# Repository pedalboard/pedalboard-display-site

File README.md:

# pedalboard-display-site

Source code for github pages avalilable from https://pedalboard.github.io/pedalboard-display-site

This is mostly generated. Do not edit directly!

* latest is generated from main
* latest-x is generated from branch x
* vX.Y.Z are the released versions
* stable points to the current stable release

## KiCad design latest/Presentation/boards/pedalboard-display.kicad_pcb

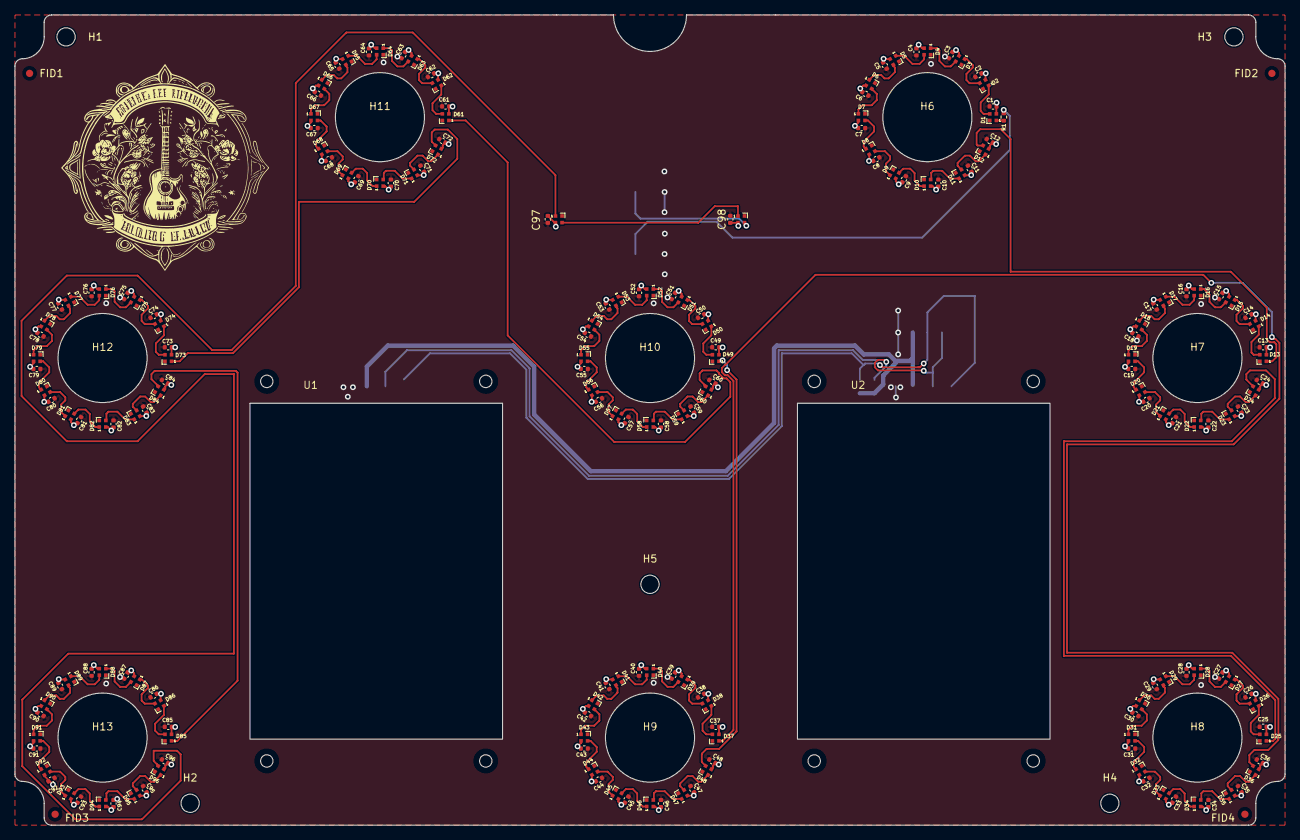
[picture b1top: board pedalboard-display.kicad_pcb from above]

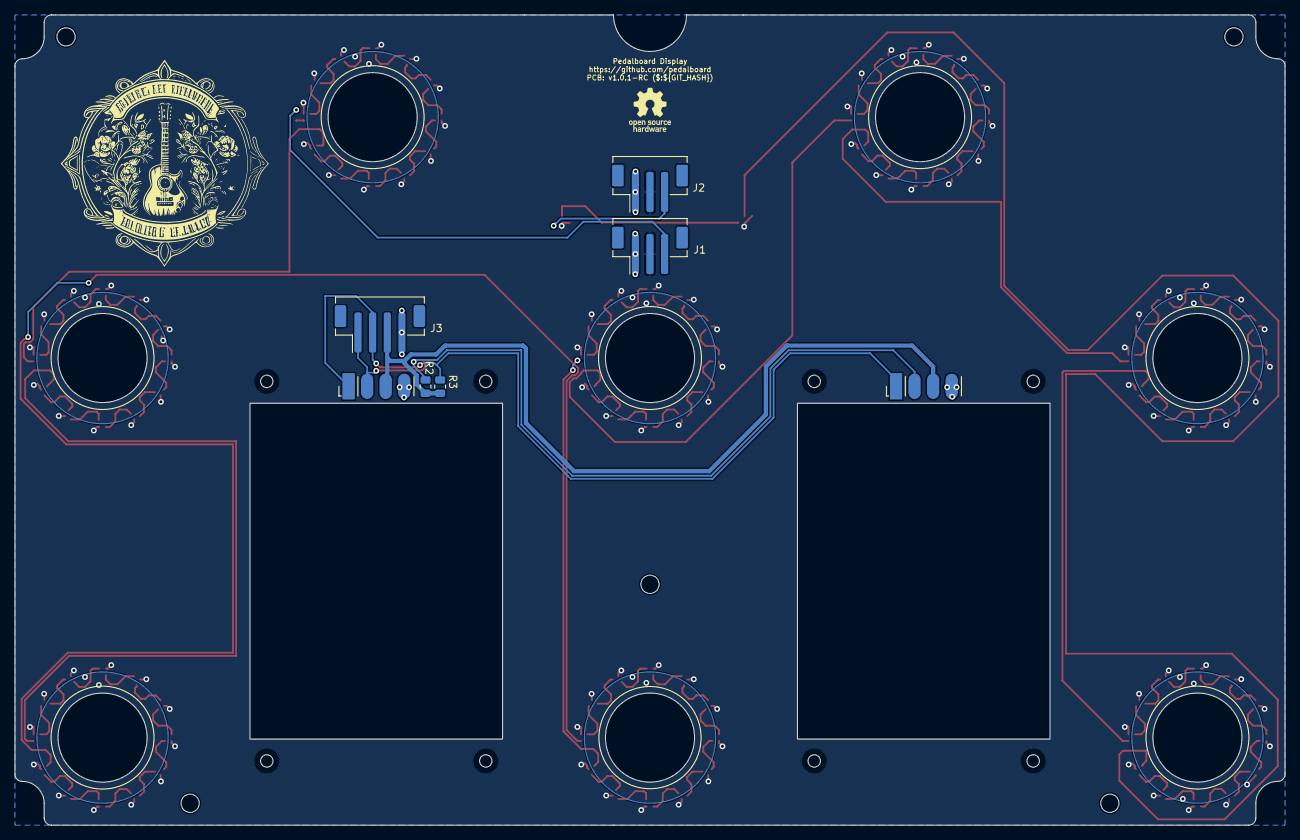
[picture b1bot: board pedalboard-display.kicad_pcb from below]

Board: 2 copper layers, 174.0 x 111.0 mm, 222 parts (6 on the bottom side), 105 nets.

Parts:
C1, C2, C3, C4, C5, C6, C7, C8, C9, C10, C11, C12, C13, C14, C15, C16, C17, C18, C19, C20, C21, C22, C23, C24, C25, C26, C27, C28, C29, C30, C31, C32, C33, C34, C35, C36, C37, C38, C39, C40, C41, C42, C43, C44, C45, C46, C47, C48, C49, C50, C51, C52, C53, C54, C55, C56, C57, C58, C59, C60, C61, C62, C63, C64, C65, C66, C67, C68, C69, C70, C71, C72, C73, C74, C75, C76, C77, C78, C79, C80, C81, C82, C83, C84, C85, C86, C87, C88, C89, C90, C91, C92, C93, C94, C95, C96, C97, C98: 1uF; C_0402_1005Metric
D1, D2, D3, D4, D5, D6, D7, D8, D9, D10, D11, D12, D13, D14, D15, D16, D17, D18, D19, D20, D21, D22, D23, D24, D25, D26, D27, D28, D29, D30, D31, D32, D33, D34, D35, D36, D37, D38, D39, D40, D41, D42, D43, D44, D45, D46, D47, D48, D49, D50, D51, D52, D53, D54, D55, D56, D57, D58, D59, D60, D61, D62, D63, D64, D65, D66, D67, D68, D69, D70, D71, D72, D73, D74, D75, D76, D77, D78, D79, D80, D81, D82, D83, D84, D85, D86, D87, D88, D89, D90, D91, D92, D93, D94, D95, D96, D97, D98: SK6812_EC15; LED_SK6812_EC15_1.5x1.5mm
FID1, FID2, FID3, FID4: Fiducial; Fiducial_1mm_Mask2mm
H1, H2, H3, H4, H5: MountingHole; MountingHole_2.5mm
H6, H11: Actuator; ActuatorRotary
H7, H8, H9, H10, H12, H13: Actuator
J1, J2: JST PH 3; JST_PH_B3B-PH-SM4-TB_1x03-1MP_P2.00mm_Vertical
J3: JST PH 4; JST_PH_B4B-PH-SM4-TB_1x04-1MP_P2.00mm_Vertical
R1: 330; R_0402_1005Metric
R2, R3: 3K3; R_0805_2012Metric
SYM1: Logo_Open_Hardware_Small; OSHW-Logo_5.7x6mm_SilkScreen
U1, U2: OLED I2C; OLED_128x128

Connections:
+3.3V: J3.3, R2.1, R3.1, U1.3 (VDD), U2.3 (VDD)
/I2C_SCL: J3.1, R2.2, U1.2 (SCL), U2.2 (SCL)
/I2C_SDA: J3.2, R3.2, U1.1 (SDA), U2.1 (SDA)
/Led Ring A/D_IN: D84.3 (DOUT), D85.1 (DIN)
/Led Ring A/D_OUT: D96.3 (DOUT), D97.1 (DIN)
/Led Ring B/D_IN: D36.3 (DOUT), D37.1 (DIN)
/Led Ring B/D_OUT: D48.3 (DOUT), D49.1 (DIN)
/Led Ring C/D_IN: D24.3 (DOUT), D25.1 (DIN)
/Led Ring D/D_IN: D72.3 (DOUT), D73.1 (DIN)
/Led Ring E/D_OUT: D60.3 (DOUT), D61.1 (DIN)
/Led Ring F/D_IN: D12.3 (DOUT), D13.1 (DIN)
/Led Ring GAIN/D_IN: D1.1 (DIN), R1.2
GND: C1.2, C2.2, C3.2, C4.2, C5.2, C6.2, C7.2, C8.2, C9.2, C10.2, C11.2, C12.2, C13.2, C14.2, C15.2, C16.2, C17.2, C18.2, C19.2, C20.2, C21.2, C22.2, C23.2, C24.2, C25.2, C26.2, C27.2, C28.2, C29.2, C30.2, C31.2, C32.2, C33.2, C34.2, C35.2, C36.2, C37.2, C38.2, C39.2, C40.2, C41.2, C42.2, C43.2, C44.2, C45.2, C46.2, C47.2, C48.2, C49.2, C50.2, C51.2, C52.2, C53.2, C54.2, C55.2, C56.2, C57.2, C58.2, C59.2, C60.2, C61.2, C62.2, C63.2, C64.2, C65.2, C66.2, C67.2, C68.2, C69.2, C70.2, C71.2, C72.2, C73.2, C74.2, C75.2, C76.2, C77.2, C78.2, C79.2, C80.2, C81.2, C82.2, C83.2, C84.2, C85.2, C86.2, C87.2, C88.2, C89.2, C90.2, C91.2, C92.2, C93.2, C94.2, C95.2, C96.2, C97.2, C98.2, D1.4 (VSS), D2.4 (VSS), D3.4 (VSS), D4.4 (VSS), D5.4 (VSS), D6.4 (VSS), D7.4 (VSS), D8.4 (VSS), D9.4 (VSS), D10.4 (VSS), D11.4 (VSS), D12.4 (VSS), D13.4 (VSS), D14.4 (VSS), D15.4 (VSS), D16.4 (VSS), D17.4 (VSS), D18.4 (VSS), D19.4 (VSS), D20.4 (VSS), D21.4 (VSS), D22.4 (VSS), D23.4 (VSS), D24.4 (VSS), D25.4 (VSS), D26.4 (VSS), D27.4 (VSS), D28.4 (VSS), D29.4 (VSS), D30.4 (VSS), D31.4 (VSS), D32.4 (VSS), D33.4 (VSS), D34.4 (VSS), D35.4 (VSS), D36.4 (VSS), D37.4 (VSS), D38.4 (VSS), D39.4 (VSS), D40.4 (VSS), D41.4 (VSS), D42.4 (VSS), D43.4 (VSS), D44.4 (VSS), D45.4 (VSS), D46.4 (VSS), D47.4 (VSS), D48.4 (VSS), D49.4 (VSS), D50.4 (VSS), D51.4 (VSS), D52.4 (VSS), D53.4 (VSS), D54.4 (VSS), D55.4 (VSS), D56.4 (VSS), D57.4 (VSS), D58.4 (VSS), D59.4 (VSS), D60.4 (VSS), D61.4 (VSS), D62.4 (VSS), D63.4 (VSS), D64.4 (VSS), D65.4 (VSS), D66.4 (VSS), D67.4 (VSS), D68.4 (VSS), D69.4 (VSS), D70.4 (VSS), D71.4 (VSS), D72.4 (VSS), D73.4 (VSS), D74.4 (VSS), D75.4 (VSS), D76.4 (VSS), D77.4 (VSS), D78.4 (VSS), D79.4 (VSS), D80.4 (VSS), D81.4 (VSS), D82.4 (VSS), D83.4 (VSS), D84.4 (VSS), D85.4 (VSS), D86.4 (VSS), D87.4 (VSS), D88.4 (VSS), D89.4 (VSS), D90.4 (VSS), D91.4 (VSS), D92.4 (VSS), D93.4 (VSS), D94.4 (VSS), D95.4 (VSS), D96.4 (VSS), D97.4 (VSS), D98.4 (VSS), J1.1, J2.1, J3.4, U1.4 (VSS), U2.4 (VSS)
unnamed: D1.3 (DOUT), D2.1 (DIN)
unnamed: D2.3 (DOUT), D3.1 (DIN)
unnamed: D3.3 (DOUT), D4.1 (DIN)
unnamed: D4.3 (DOUT), D5.1 (DIN)
unnamed: D5.3 (DOUT), D6.1 (DIN)
unnamed: D6.3 (DOUT), D7.1 (DIN)
unnamed: D7.3 (DOUT), D8.1 (DIN)
unnamed: D8.3 (DOUT), D9.1 (DIN)
unnamed: D9.3 (DOUT), D10.1 (DIN)
unnamed: D10.3 (DOUT), D11.1 (DIN)
unnamed: D11.3 (DOUT), D12.1 (DIN)
unnamed: D13.3 (DOUT), D14.1 (DIN)
unnamed: D14.3 (DOUT), D15.1 (DIN)
unnamed: D15.3 (DOUT), D16.1 (DIN)
unnamed: D16.3 (DOUT), D17.1 (DIN)
unnamed: D17.3 (DOUT), D18.1 (DIN)
unnamed: D18.3 (DOUT), D19.1 (DIN)
unnamed: D19.3 (DOUT), D20.1 (DIN)
unnamed: D20.3 (DOUT), D21.1 (DIN)
unnamed: D21.3 (DOUT), D22.1 (DIN)
unnamed: D22.3 (DOUT), D23.1 (DIN)
unnamed: D23.3 (DOUT), D24.1 (DIN)
unnamed: D25.3 (DOUT), D26.1 (DIN)
unnamed: D26.3 (DOUT), D27.1 (DIN)
unnamed: D27.3 (DOUT), D28.1 (DIN)
unnamed: D28.3 (DOUT), D29.1 (DIN)
unnamed: D29.3 (DOUT), D30.1 (DIN)
unnamed: D30.3 (DOUT), D31.1 (DIN)
unnamed: D31.3 (DOUT), D32.1 (DIN)
unnamed: D32.3 (DOUT), D33.1 (DIN)
unnamed: D33.3 (DOUT), D34.1 (DIN)
unnamed: D34.3 (DOUT), D35.1 (DIN)
unnamed: D35.3 (DOUT), D36.1 (DIN)
unnamed: D37.3 (DOUT), D38.1 (DIN)
unnamed: D38.3 (DOUT), D39.1 (DIN)
unnamed: D39.3 (DOUT), D40.1 (DIN)
unnamed: D40.3 (DOUT), D41.1 (DIN)
unnamed: D41.3 (DOUT), D42.1 (DIN)
unnamed: D42.3 (DOUT), D43.1 (DIN)
unnamed: D43.3 (DOUT), D44.1 (DIN)
unnamed: D44.3 (DOUT), D45.1 (DIN)
unnamed: D45.3 (DOUT), D46.1 (DIN)
unnamed: D46.3 (DOUT), D47.1 (DIN)
unnamed: D47.3 (DOUT), D48.1 (DIN)
unnamed: D49.3 (DOUT), D50.1 (DIN)
unnamed: D50.3 (DOUT), D51.1 (DIN)
unnamed: D51.3 (DOUT), D52.1 (DIN)
unnamed: D52.3 (DOUT), D53.1 (DIN)
unnamed: D53.3 (DOUT), D54.1 (DIN)
unnamed: D54.3 (DOUT), D55.1 (DIN)
unnamed: D55.3 (DOUT), D56.1 (DIN)
unnamed: D56.3 (DOUT), D57.1 (DIN)
unnamed: D57.3 (DOUT), D58.1 (DIN)
unnamed: D58.3 (DOUT), D59.1 (DIN)
unnamed: D59.3 (DOUT), D60.1 (DIN)
unnamed: D61.3 (DOUT), D62.1 (DIN)
unnamed: D62.3 (DOUT), D63.1 (DIN)
unnamed: D63.3 (DOUT), D64.1 (DIN)
unnamed: D64.3 (DOUT), D65.1 (DIN)
unnamed: D65.3 (DOUT), D66.1 (DIN)
unnamed: D66.3 (DOUT), D67.1 (DIN)
unnamed: D67.3 (DOUT), D68.1 (DIN)
unnamed: D68.3 (DOUT), D69.1 (DIN)
unnamed: D69.3 (DOUT), D70.1 (DIN)
unnamed: D70.3 (DOUT), D71.1 (DIN)
unnamed: D71.3 (DOUT), D72.1 (DIN)
unnamed: D73.3 (DOUT), D74.1 (DIN)
unnamed: D74.3 (DOUT), D75.1 (DIN)
unnamed: D75.3 (DOUT), D76.1 (DIN)
unnamed: D76.3 (DOUT), D77.1 (DIN)
unnamed: D77.3 (DOUT), D78.1 (DIN)
unnamed: D78.3 (DOUT), D79.1 (DIN)
unnamed: D79.3 (DOUT), D80.1 (DIN)
unnamed: D80.3 (DOUT), D81.1 (DIN)
unnamed: D81.3 (DOUT), D82.1 (DIN)
unnamed: D82.3 (DOUT), D83.1 (DIN)
unnamed: D83.3 (DOUT), D84.1 (DIN)
unnamed: D85.3 (DOUT), D86.1 (DIN)
unnamed: D86.3 (DOUT), D87.1 (DIN)
unnamed: D87.3 (DOUT), D88.1 (DIN)
unnamed: D88.3 (DOUT), D89.1 (DIN)
unnamed: D89.3 (DOUT), D90.1 (DIN)
unnamed: D90.3 (DOUT), D91.1 (DIN)
unnamed: D91.3 (DOUT), D92.1 (DIN)
unnamed: D92.3 (DOUT), D93.1 (DIN)
unnamed: D93.3 (DOUT), D94.1 (DIN)
unnamed: D94.3 (DOUT), D95.1 (DIN)
unnamed: D95.3 (DOUT), D96.1 (DIN)
unnamed: D97.3 (DOUT), D98.1 (DIN)
unnamed: D98.3 (DOUT), J2.3
unnamed: J1.3, R1.1
VCC: C1.1, C2.1, C3.1, C4.1, C5.1, C6.1, C7.1, C8.1, C9.1, C10.1, C11.1, C12.1, C13.1, C14.1, C15.1, C16.1, C17.1, C18.1, C19.1, C20.1, C21.1, C22.1, C23.1, C24.1, C25.1, C26.1, C27.1, C28.1, C29.1, C30.1, C31.1, C32.1, C33.1, C34.1, C35.1, C36.1, C37.1, C38.1, C39.1, C40.1, C41.1, C42.1, C43.1, C44.1, C45.1, C46.1, C47.1, C48.1, C49.1, C50.1, C51.1, C52.1, C53.1, C54.1, C55.1, C56.1, C57.1, C58.1, C59.1, C60.1, C61.1, C62.1, C63.1, C64.1, C65.1, C66.1, C67.1, C68.1, C69.1, C70.1, C71.1, C72.1, C73.1, C74.1, C75.1, C76.1, C77.1, C78.1, C79.1, C80.1, C81.1, C82.1, C83.1, C84.1, C85.1, C86.1, C87.1, C88.1, C89.1, C90.1, C91.1, C92.1, C93.1, C94.1, C95.1, C96.1, C97.1, C98.1, D1.2 (VDD), D2.2 (VDD), D3.2 (VDD), D4.2 (VDD), D5.2 (VDD), D6.2 (VDD), D7.2 (VDD), D8.2 (VDD), D9.2 (VDD), D10.2 (VDD), D11.2 (VDD), D12.2 (VDD), D13.2 (VDD), D14.2 (VDD), D15.2 (VDD), D16.2 (VDD), D17.2 (VDD), D18.2 (VDD), D19.2 (VDD), D20.2 (VDD), D21.2 (VDD), D22.2 (VDD), D23.2 (VDD), D24.2 (VDD), D25.2 (VDD), D26.2 (VDD), D27.2 (VDD), D28.2 (VDD), D29.2 (VDD), D30.2 (VDD), D31.2 (VDD), D32.2 (VDD), D33.2 (VDD), D34.2 (VDD), D35.2 (VDD), D36.2 (VDD), D37.2 (VDD), D38.2 (VDD), D39.2 (VDD), D40.2 (VDD), D41.2 (VDD), D42.2 (VDD), D43.2 (VDD), D44.2 (VDD), D45.2 (VDD), D46.2 (VDD), D47.2 (VDD), D48.2 (VDD), D49.2 (VDD), D50.2 (VDD), D51.2 (VDD), D52.2 (VDD), D53.2 (VDD), D54.2 (VDD), D55.2 (VDD), D56.2 (VDD), D57.2 (VDD), D58.2 (VDD), D59.2 (VDD), D60.2 (VDD), D61.2 (VDD), D62.2 (VDD), D63.2 (VDD), D64.2 (VDD), D65.2 (VDD), D66.2 (VDD), D67.2 (VDD), D68.2 (VDD), D69.2 (VDD), D70.2 (VDD), D71.2 (VDD), D72.2 (VDD), D73.2 (VDD), D74.2 (VDD), D75.2 (VDD), D76.2 (VDD), D77.2 (VDD), D78.2 (VDD), D79.2 (VDD), D80.2 (VDD), D81.2 (VDD), D82.2 (VDD), D83.2 (VDD), D84.2 (VDD), D85.2 (VDD), D86.2 (VDD), D87.2 (VDD), D88.2 (VDD), D89.2 (VDD), D90.2 (VDD), D91.2 (VDD), D92.2 (VDD), D93.2 (VDD), D94.2 (VDD), D95.2 (VDD), D96.2 (VDD), D97.2 (VDD), D98.2 (VDD), J1.2, J2.2

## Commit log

2024-10-04 Deploying to main from @ pedalboard/pedalboard-display@410cee6008e3cf2b650e44362ccc1691f1291ad5 🚀
2024-10-04 Deploying to main from @ pedalboard/pedalboard-display@4f9086a0ea0e011ea406c3ff693b5c56c862ad1e 🚀
2024-10-04 Deploying to main from @ pedalboard/pedalboard-display@2bf41b55ac07e01ddf97c7d10a7e1ace507452db 🚀
2024-10-05 Deploying to main from @ pedalboard/pedalboard-display@fb8f41156457d44ac85662de3aa29290168164b6 🚀
2024-10-05 Deploying to main from @ pedalboard/pedalboard-display@69fa1f91c95806fd53bbb4cf03f6fd2894108b53 🚀
2024-10-05 Deploying to main from @ pedalboard/pedalboard-display@f8f95626dab1886cdfae880860ee8407afd30411 🚀
2024-10-06 Deploying to main from @ pedalboard/pedalboard-display@386c9de8feedf041a3b9a95ac1bfa1e5dc5e144d 🚀
2024-10-06 Deploying to main from @ pedalboard/pedalboard-display@27b15ea97f876563fadd0e18eeba4676c72a604f 🚀
2024-10-06 Deploying to main from @ pedalboard/pedalboard-display@5a65175c090419f12d399ef1516610d396a1ab5b 🚀
2024-10-06 Deploying to main from @ pedalboard/pedalboard-display@56bcfcf3832946813410f151d339cac758fd9e4f 🚀
2024-10-06 Deploying to main from @ pedalboard/pedalboard-display@e876ba0202e51abd809a469285fc4262403e3e5e 🚀
2024-10-06 Deploying to main from @ pedalboard/pedalboard-display@dc074c0cbfff559bdaca82b6a3adb7c944f90245 🚀
2024-10-06 Deploying to main from @ pedalboard/pedalboard-display@c057cef7ac1ceddc983e4d5d4dfae9bc996736da 🚀
2024-10-06 Deploying to main from @ pedalboard/pedalboard-display@e0192e1d66e4018c6423af936adf27e5b0b6d0b1 🚀
2024-10-06 Deploying to main from @ pedalboard/pedalboard-display@1b8568462cefc59b877d0567eee6cc9eafeb2546 🚀
2024-10-06 Deploying to main from @ pedalboard/pedalboard-display@0b437a313edb1eda0cee02ba7c8a9dc4beacf278 🚀
2024-10-06 Deploying to main from @ pedalboard/pedalboard-display@f2215149ee8fa1761b8102f340bb922b52d0c975 🚀
2024-10-06 Deploying to main from @ pedalboard/pedalboard-display@f60ebcb4e3c80d8be295d4f5d56c3c9cb2e1f262 🚀
2024-10-06 Deploying to main from @ pedalboard/pedalboard-display@25d815b7b5fb85007704c4cd4ddb0a1ddef54c2a 🚀
2024-10-06 Deploying to main from @ pedalboard/pedalboard-display@fbaca728853fdd4bc852988fd786f962d6e50449 🚀
2024-10-06 Deploying to main from @ pedalboard/pedalboard-display@f11800b69cc1d232d4cb8142cff629dfbacd3cb2 🚀
2024-10-06 Deploying to main from @ pedalboard/pedalboard-display@8c20be24a42984ca690cb9967ec994ccf1ce5837 🚀
2024-10-07 Deploying to main from @ pedalboard/pedalboard-display@ed5daf3a73271a1219396e5281b2c6e43b89c100 🚀
2024-10-08 Deploying to main from @ pedalboard/pedalboard-display@858d2dd1fb463c75b27bccf2da3ce8923a7aeb58 🚀
2024-10-08 Deploying to main from @ pedalboard/pedalboard-display@4d68c468bef59009f4bc5b47d1dc6559f2bea8d9 🚀
2024-10-08 Deploying to main from @ pedalboard/pedalboard-display@be39d3a58bf92c60c8e9bd36fad391724423109d 🚀
2024-10-08 Deploying to main from @ pedalboard/pedalboard-display@7a7ece845551832e3e792c21678fe6d100b4696e 🚀
2024-10-08 Deploying to main from @ pedalboard/pedalboard-display@a01648c17aa75a8a1f5b85c9c13e135b939d5d71 🚀
2024-10-08 Deploying to main from @ pedalboard/pedalboard-display@28cdf0d12fbcfe2a0dee687aaca92cc09587cc0b 🚀
2024-10-08 Deploying to main from @ pedalboard/pedalboard-display@e0f137995197d599507c3dd5179f08441716a99e 🚀
2024-10-08 Deploying to main from @ pedalboard/pedalboard-display@17886c2355e44c863d8ead2ce34bcd6f35372db4 🚀
2024-10-08 Deploying to main from @ pedalboard/pedalboard-display@8a22f3d6358bb323decbb24202d683f1d61aad72 🚀
2024-10-08 Deploying to main from @ pedalboard/pedalboard-display@98c524074379a9414fd13bcdc52381adf38a0e94 🚀
2024-10-09 Deploying to main from @ pedalboard/pedalboard-display@782110e533f588448b6cd7407100523902cc09cc 🚀
2024-10-09 Deploying to main from @ pedalboard/pedalboard-display@96aa024edd11246be503d7e1a8a611206f1687a7 🚀
2024-10-13 Deploying to main from @ pedalboard/pedalboard-display@24ab52845f2b16743cca9cc7f41b850b85bf700b 🚀
2024-10-14 Deploying to main from @ pedalboard/pedalboard-display@0217376f41d17617869b6aa0874cad9b65e1d7cd 🚀
2024-10-15 Deploying to main from @ pedalboard/pedalboard-display@459c2295644c288ef4d841c9a5e45bdab20f18ff 🚀
2024-10-15 Deploying to main from @ pedalboard/pedalboard-display@42dc037ea1e30a0288a741ab2a66edf7ee306c43 🚀
2024-10-15 Deploying to main from @ pedalboard/pedalboard-display@bd993425f30c5961447cadb568e5c24ce05211e9 🚀
2024-10-15 Deploying to main from @ pedalboard/pedalboard-display@8ef4bbe3759b260ccef78baed2d796115ff1481e 🚀
2024-10-15 Deploying to main from @ pedalboard/pedalboard-display@84f4df328e9342b0b5fb9289e5789f326067643a 🚀
2024-10-15 Deploying to main from @ pedalboard/pedalboard-display@427318e428172410eb44a377b1f2a940c69a2fd8 🚀
2024-10-16 Deploying to main from @ pedalboard/pedalboard-display@88b9b02c9c6b1ac4ea716c600346aba88077f420 🚀
2024-10-16 Deploying to main from @ pedalboard/pedalboard-display@45c584ff948b376296df0969ae1c252126cca136 🚀
2024-10-16 v1.0.0
2024-10-17 Deploying to main from @ pedalboard/pedalboard-display@84a78cd54d30ba06f3ff6b812d09c0aadd561d98 🚀
2024-10-17 Deploying to main from @ pedalboard/pedalboard-display@ed3734ce3d0df49cb64748a579eb3f9c6220c56b 🚀
2024-10-17 Deploying to main from @ pedalboard/pedalboard-display@c1891d69b255ff34682b8087a0282670555ebd9c 🚀
2024-12-15 Deploying to main from @ pedalboard/pedalboard-display@c057869bc666828a260b41d334b71f5a277ae765 🚀
2024-12-16 Deploying to main from @ pedalboard/pedalboard-display@801a87c80af120991ef4bc0bf08306d4e8891684 🚀
2024-12-24 Deploying to main from @ pedalboard/pedalboard-display@2a51bc55f1169eaa586e90c363b15b60a091e573 🚀
2025-04-21 Deploying to main from @ pedalboard/pedalboard-display@aee31764f72741e6697704d457c2198dc5ab8179 🚀
2025-04-21 Deploying to main from @ pedalboard/pedalboard-display@328f9c58fba1435ce04091152acafb586bf9fd22 🚀
2026-04-14 Redirect to pedalboard-display gh-pages

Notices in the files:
latest/Presentation/boards/pedalboard-display.kicad_pcb:
License: CERN Open Hardware Licence Version 2 - Permissive
